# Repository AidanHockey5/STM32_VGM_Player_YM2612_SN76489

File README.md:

# This Version of the Project is now Deprecated
This is the old version of the Mega Blaster Project. Please visit this repo for the latest and greatest Mega Blaster 2 source material
https://github.com/AidanHockey5/MegaBlaster2

# Mega Blaster

See this project in action here: https://www.youtube.com/watch?v=WoAp2-gWaLM

For more information, visit: http://www.aidanlawrence.com/megablaster-hardware-sega-genesis-video-game-music-player/

This project is a hardware Video Game Music (VGM) player that uses a genuine YM2612 synthesizer chip + SN76489AN PSG. 
This project is driven by an STM32 "Blue Pill" board, chosen for it's ample speed, I/O, and best of all, price!

Included in this repository is the source code for the project, all of the schematic files, and a completed 
Ki-CAD printed circuit board /w Gerber files. Feel free to produce your own board!

# Information about the main sound chips and VGM

The YM2612 is a 6-channel FM synthesizer IC that was most prominently featured in the Sega Genesis (AKA Megadrive) home video game console. The YM2612 was also featured in the FM-Towns home computer and the Sega C2 Arcade System.
The YM2612 also had a CMOS alias that is functionally identical named the YM3438.
The SN76489 is a 3-channel + 1 noise channel programmable sound generator (PSG) that was popular with several early video game systems and home computers.
Most notably, the SN76489 was featured in the Sega Master system, the predecessor to the Genesis. To allow for backwards compatibility, Sega included a clone of the SN76489 in their new Genesis consoles.
Programmers and sound designers could leverage the SN76489 to add three more square wave channels to the YM2612's 6-channels of FM synth, creating 9 channels + 1 noise channels in total.
While this player was designed with the Genesis in mind, it can play back any VGM files designed for the Master System, FM-Towns PC, C2 machine, or any other machine that used the YM2612/YM3438 and/or the SN76489.
This project synthesizes music from .VGM files in real time on genuine hardware. There is no emulation here.

VGM stands for Video Game Music, and it is a 44.1KHz logging format that stores real soundchip register information. My player will parse these files and send the data to the appropriate chips. You can learn more about the VGM file format here: http://www.smspower.org/Music/VGMFileFormat

http://www.smspower.org/uploads/Music/vgmspec170.txt?sid=58da937e68300c059412b536d4db2ca0

# SD Card Information
This project is built for full-sized SD cards, but you may use adapters to fit your desired card. You must format your SD card to Fat32 in order for this device to work correctly. Your SD card must only contain uncompressed .vgm files. VGZ FILES WILL NOT WORK! You may download .vgz files and use [7zip](http://www.7-zip.org/download.html) to extract the uncompressed file out of them. Vgm files on the SD card do not need to have the .vgm extension. As long as they contain valid, uncompressed vgm data, they will be read by the program regardless of their name.
You can find VGM files by Googling "myGameName VGM," or by checking out sites like http://vgmrips.net/packs/

# Control Over Serial
You can use a serial connection to control playback features. The commands are as follows:

Command | Result
------------ | -------------
\+ | Next Track
\- | Previous Track
\* | Random Track
\/ | Toggle Shuffle Mode
\. | Toggle Song Looping
r: | Request song
? | What song is playing?
\! | Toggle the OLED display

A song request is formatted as follows: ```r:mySongFile.vgm```
Once a song request is sent through the serial console, an attempt will be made to open that song file. The file must exist on the SD card, and spelling/capitalization must be correct.
Need an easy-to-use serial console? [I've made one here.](https://github.com/AidanHockey5/OpenArduinoSerialConsole)

# Schematic

[PDF](https://github.com/AidanHockey5/STM32_VGM_Player_YM2612_SN76489/raw/master/Schematics/STM32_MegaBlaster/STM32_MegaBlaster.pdf)

[Bill Of Materials (BOM)](https://github.com/AidanHockey5/STM32_VGM_Player_YM2612_SN76489/tree/master/Schematics/STM32_MegaBlaster/BOM)

# Interactive Assembly Guide
[You can view the interactive guide here.](https://www.aidanlawrence.com/wp-content/uploads/2018/09/ibom.html)

Courtesy of the stellar KiCAD plugin, [Interactive HTML BOM](https://github.com/openscopeproject/InteractiveHtmlBom)

Use this guide to help you assemble the Mega Blaster. Hover your cursor over the list of parts and this web page will show you where to place each component. I have included the source HTML file under the [Schematic's BOM folder](https://github.com/AidanHockey5/STM32_VGM_Player_YM2612_SN76489/tree/master/Schematics/STM32_MegaBlaster/BOM) for local viewing. 

# Programming

Programming must be done through the built-in serial port. YOU CAN NOT USE AN STLINK FOR PROGRAMMING.

You have two programming options: Using the flashing tool OR flashing from source.

[DOWNLOAD THE FLASHING TOOL HERE](https://www.aidanlawrence.com/tools/ee/megablaster/MegaFlasher_MB.zip)

Windows users can just use the pre-compiled Flash.exe program to skip worrying about Python installs or dependancies.
All other operating system users can simply run the Flash.py script using Python 3.0+.

Read the Readme file included with the tool for usage instructions and python dependancies.

I have also made a quick video guide on how to program the MegaBlaster from source. It's pretty simple!

https://youtu.be/sSx3_d5n6gs

1) Set the "Bluepill" left jumper to the '1' position.
2) Turn on the MegaBlaster
3) Hit the reset button on the Bluepill board.
4) Open the source code in Visual Studio Code /w the PlatformIO extension.
5) Upload the code using the upload button on the bottom ribbon.
6) Replace the jumper on the Bluepill board to it's original '0' position.

Link to VS Code: https://code.visualstudio.com/

PlatformIO install guide: http://docs.platformio.org/en/latest/ide/vscode.html#installation 

PlatformIO Not finding your serial port? Try opening up your Platformio.ini file and adding the following lines:
```
upload_port = COMX

upload_protocol = serial
```

(Make sure to change 'X' to the number of your COM port that the MegaBlaster is connected to. (I.E. COM4, COM8, COM10, etc.)

# KiCad
The schematic and PCB of this project was made in a nightly version of KiCad 5, specifically, 5.0.0 RC2 (dev-493-gd776eaca8)
Since then, the project has been migrated to KiCAD 5 stable.
Please download the latest stable release of KiCAD 5 here: http://kicad-pcb.org/download/

# YM3438 Support
After a little tinkering, I've managed to get a YM3438 working as a replacement for the YM2612. For those that don't know, the YM3438 is functionally equivalent to the YM2612, but is made using a CMOS process. The YM3438 is pin-compatible but it is not a drop-in replacement since the output impedance is significantly higher. Fortunately, all you need to do to get a YM3438 to work is mod a couple resistors.

Resistor Number | Replace with
------------ | -------------
R7 | LEAVE UNPOPULATED
R8 | LEAVE UNPOPULATED
R6 | 1.2K
R9 | 100K
R10 | 100K
R27 | 33K
R30 | 33K
R28 | 150K
R29 | 150K

WARNING! The final sound output volume will be SIGNIFICANTLY HIGHER with this setup. Be sure to start your YM3438 MegaBlaster at the lowest possible volume before turning on the device and slowly increase the volume to prevent equipment damage and or hearing damage.

Why replace the YM2612 with a YM3438? Well, for one, the YM3438 runs very cool while the YM2612s typically get screaming hot during normal operation. The sound quality is also slightly altered with FM synths typically sounding a little more 'sterile' compared to the YM2612's characteristic grit. PCM sample quality is also significantly improved. Later revisions of the Sega Genesis used an ASIC YM3438 instead of a discrete YM2612, so some users may be more familiar with the likes of the YM3438 than the YM2612. It's all personal preference really.

You can see a YM2612/YM3438 comparison video here: https://www.youtube.com/watch?v=jMHRtriv1wM

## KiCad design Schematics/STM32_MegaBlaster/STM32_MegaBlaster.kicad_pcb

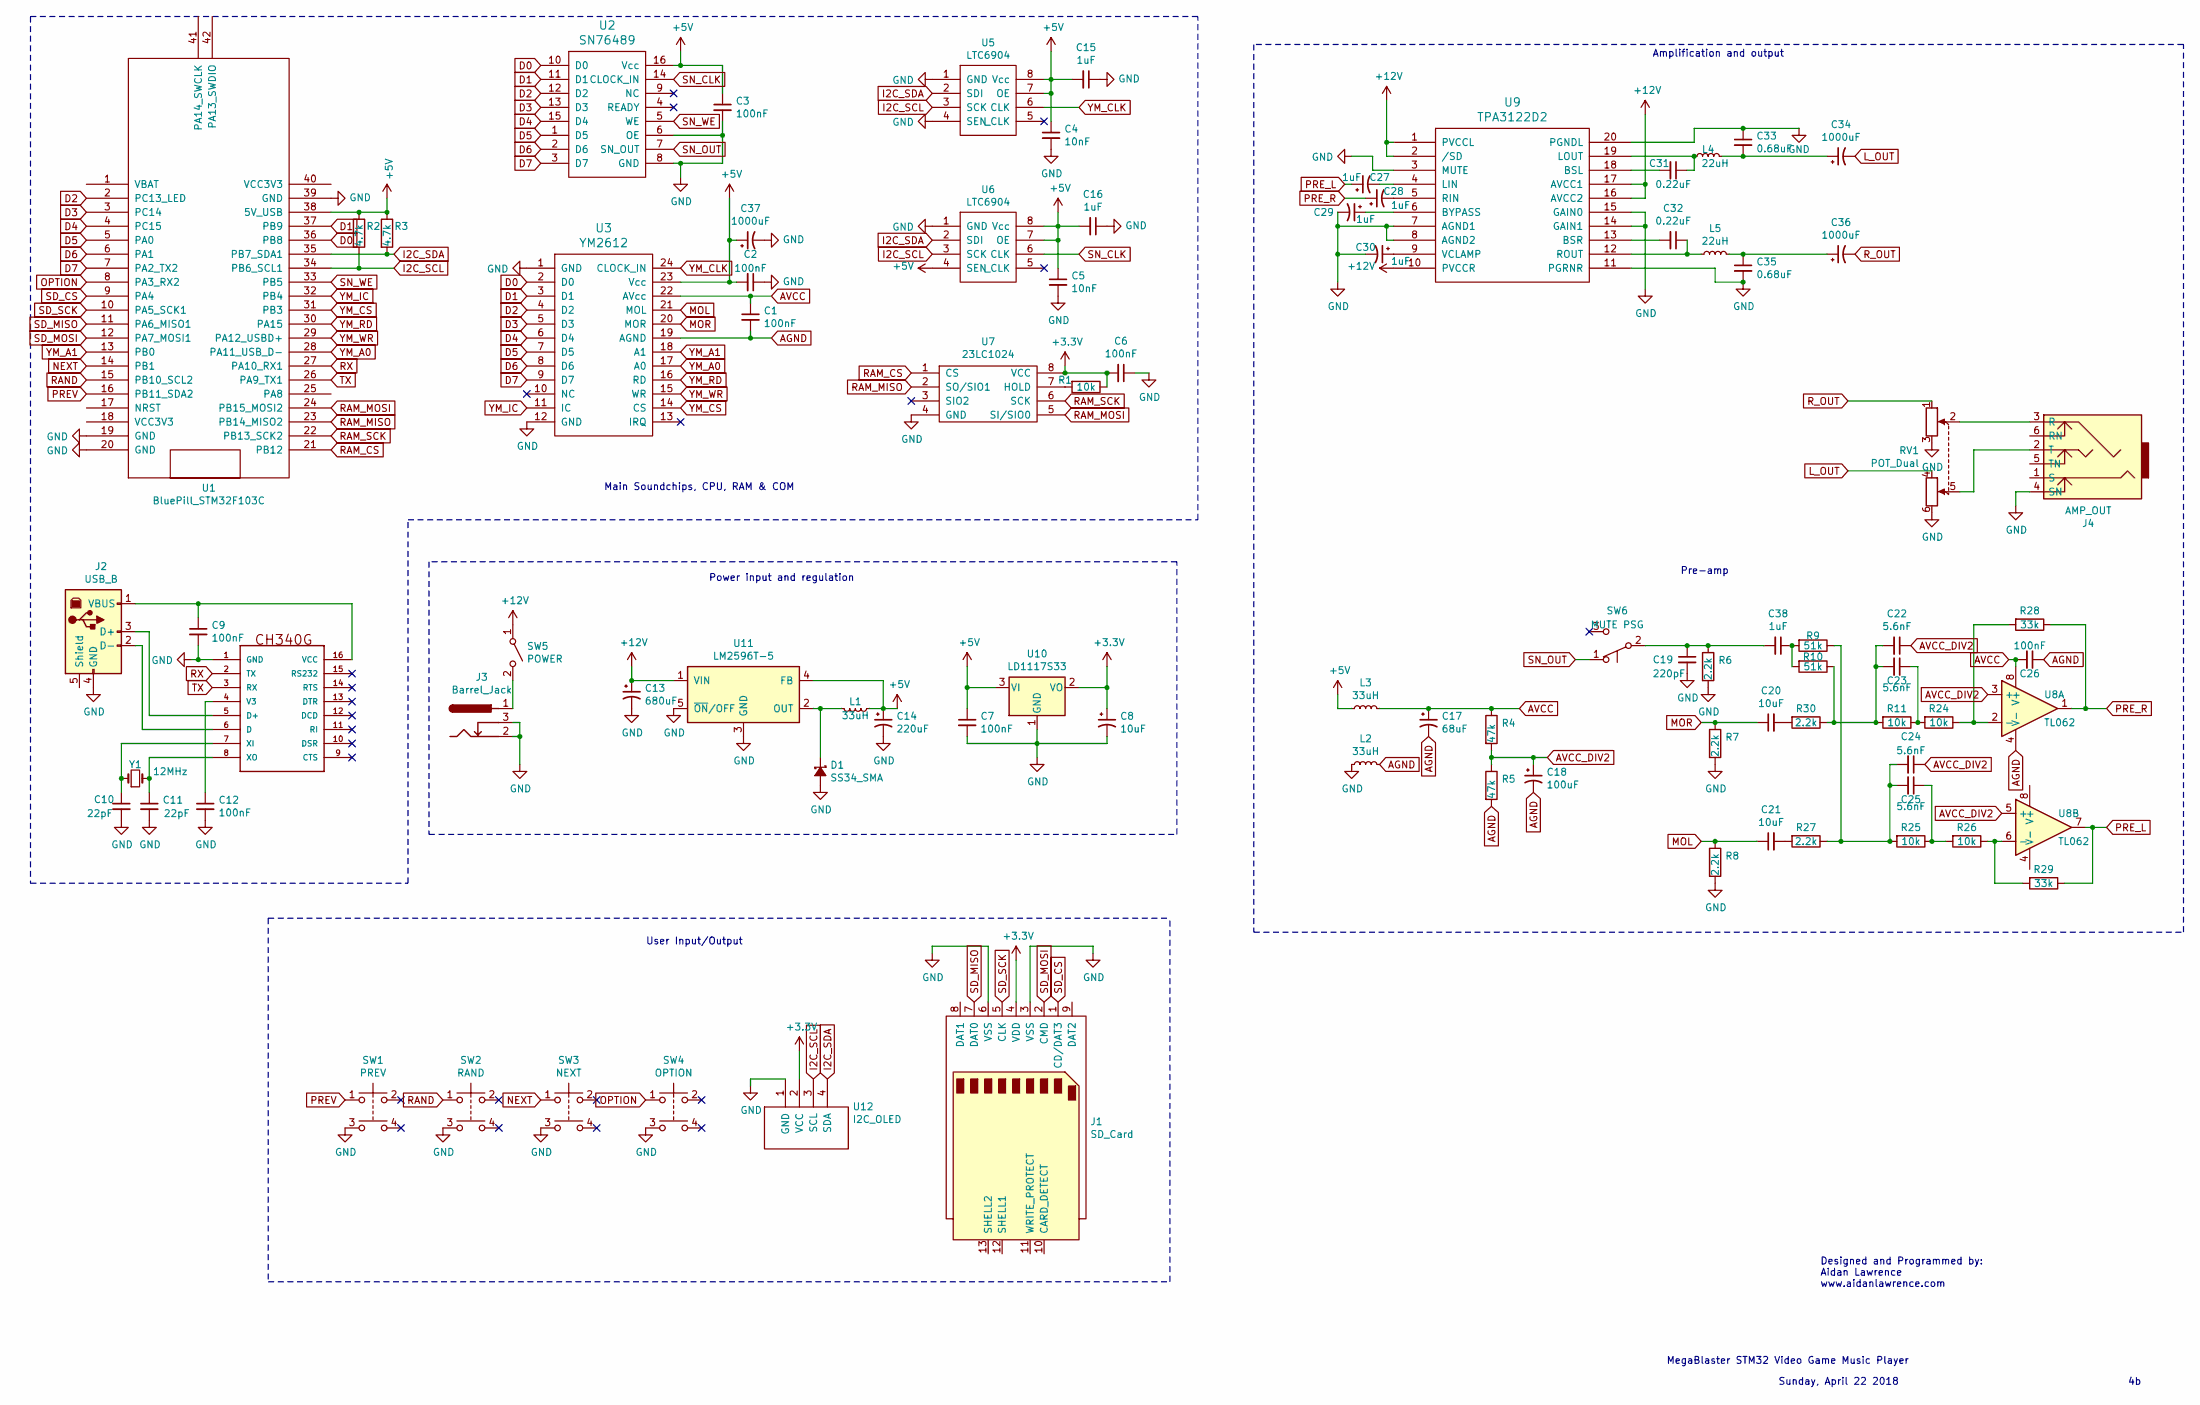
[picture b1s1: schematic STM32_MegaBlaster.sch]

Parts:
C1, C2, C6, C7, C9, C12, C26: 100nF; C_Disc_D3.0mm_W1.6mm_P2.50mm
C3: 100nF; C_Axial_L22.0mm_D10.5mm_P27.50mm_Horizontal
C4, C5: 10nF; C_Disc_D3.0mm_W1.6mm_P2.50mm
C8: 10uF; CP_Radial_D4.0mm_P1.50mm
C10, C11: 22pF; C_Disc_D3.0mm_W1.6mm_P2.50mm
C13: 680uF; CP_Radial_D10.0mm_P5.00mm
C14: 220uF; CP_Radial_D6.3mm_P2.50mm
C15, C16, C38: 1uF; C_Disc_D4.7mm_W2.5mm_P5.00mm
C17: 68uF; CP_Radial_D6.3mm_P2.50mm
C18: 100uF; CP_Radial_D5.0mm_P2.00mm
C19: 220pF; C_Disc_D4.7mm_W2.5mm_P5.00mm
C20, C21: 10uF; C_Disc_D4.7mm_W2.5mm_P5.00mm
C22, C23, C24, C25: 5.6nF; C_Disc_D4.7mm_W2.5mm_P5.00mm
C27, C28, C29, C30: 1uF; CP_Radial_D4.0mm_P1.50mm
C31, C32: 0.22uF; C_Disc_D4.7mm_W2.5mm_P5.00mm
C33: 0.68uF; C_Disc_D3.0mm_W1.6mm_P2.50mm
C34, C36, C37: 1000uF; CP_Radial_D8.0mm_P2.50mm
C35: 0.68uF; CP_Radial_D6.3mm_P2.50mm
D1: SS34_SMA; D_SOD-123F
J1: SD_Card; SD_TE_2041021
J2: USB_B
J3: Barrel_Jack; BARREL_JACK
J4: AMP_OUT; PJ320E_3.5mm_Jack
L1, L2, L3: 33uH; L_Radial_D7.0mm_P3.00mm
L4, L5: 22uH; L_Radial_D8.7mm_P5.00mm_Fastron_07HCP
R1, R11, R24, R25, R26: 10k; R_Axial_DIN0207_L6.3mm_D2.5mm_P7.62mm_Horizontal
R2, R3: 4.7k; R_Axial_DIN0207_L6.3mm_D2.5mm_P7.62mm_Horizontal
R4, R5: 47k; R_Axial_DIN0207_L6.3mm_D2.5mm_P7.62mm_Horizontal
R6, R7, R8, R27, R30: 2.2k; R_Axial_DIN0207_L6.3mm_D2.5mm_P7.62mm_Horizontal
R9, R10: 51k; R_Axial_DIN0207_L6.3mm_D2.5mm_P7.62mm_Horizontal
R28, R29: 33k; R_Axial_DIN0207_L6.3mm_D2.5mm_P7.62mm_Horizontal
RV1: POT_Dual; Potentiometer_Alps_RK163_Double_Vertical
SW1: PREV; SW_TH_Tactile_Omron_B3F-10xx
SW2: RAND; SW_TH_Tactile_Omron_B3F-10xx
SW3: NEXT; SW_TH_Tactile_Omron_B3F-10xx
SW4: OPTION; SW_TH_Tactile_Omron_B3F-10xx
SW5: POWER; 1825115-1
SW6: MUTE PSG; 1825115-1
U1: BluePill_STM32F103C
U2: SN76489; DIP-16_W7.62mm
U3: YM2612; DIP-24_W15.24mm
U4: CH340G; SOIC16
U5, U6: LTC6904; MSOP-8_3x3mm_Pitch0.65mm
U7: 23LC1024; DIP-8_W7.62mm
U8: TL062; DIP-8_W7.62mm
U9: TPA3122D2; DIP-20_W7.62mm
U10: LD1117S33; SOT-223-3_TabPin2
U11: LM2596T-5; TO170P1435X465-6N
U12: I2C_OLED; 1_3_Inch_I2C_OLED
Y1: 12MHz; Crystal_HC49-U_Vertical

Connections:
+3V3: C6.2, C8.1, J1.4 (VDD), R1.1, U7.8 (VCC), U10.2 (VO), U12.2 (VCC)
+5V: C2.2, C3.1, C4.1, C5.1, C7.1, C14.1, C15.2, C16.2, C37.1, L1.1, L3.1, R2.1, R3.1, U1.38 (5V_USB), U2.16 (Vcc), U3.23 (Vcc), U5.7 (OE), U5.8 (Vcc), U6.4 (SEN), U6.7 (OE), U6.8 (Vcc), U10.3 (VI), U11.4 (FB)
+12V: C13.1, SW5.1 (A), U9.1 (PVCCL), U9.2 (/SD), U9.10 (PVCCR), U9.16 (AVCC2), U9.17 (AVCC1), U11.1 (VIN)
AGND: C1.2, C17.2, C18.2, C26.1, L2.2, R5.2, U3.19 (AGND), U8.4 (V-)
AVCC: C1.1, C17.1, C26.2, L3.2, R4.1, U3.22 (AVcc), U8.8 (V+)
AVCC_DIV2: C18.1, C22.1, C24.1, R4.2, R5.1, U8.3 (+), U8.5 (+)
D0: U1.36 (PB8), U2.10 (D0), U3.2 (D0)
D1: U1.37 (PB9), U2.11 (D1), U3.3 (D1)
D2: U1.2 (PC13_LED), U2.12 (D2), U3.4 (D2)
D3: U1.3 (PC14), U2.13 (D3), U3.5 (D3)
D4: U1.4 (PC15), U2.15 (D4), U3.6 (D4)
D5: U1.5 (PA0), U2.1 (D5), U3.7 (D5)
D6: U1.6 (PA1), U2.2 (D6), U3.8 (D6)
D7: U1.7 (PA2_TX2), U2.3 (D7), U3.9 (D7)
GND: C2.1, C3.2, C4.2, C5.2, C6.1, C7.2, C8.2, C9.2, C10.2, C11.2, C12.2, C13.2, C14.2, C15.1, C16.1, C19.2, C29.2, C30.2, C33.1, C35.2, C37.2, D1.2 (A), J1.3 (VSS), J1.6 (VSS), J2.4 (GND), J3.2, J3.3, J4.3 (R), J4.4 (SN), L2.1, R6.2, R7.2, R8.2, RV1.2, RV1.3, RV1.6, SW1.3, SW2.3, SW3.3, SW4.3, U1.19 (GND), U1.20 (GND), U1.39 (GND), U2.6 (OE), U2.8 (GND), U3.1 (GND), U3.12 (GND), U4.1 (GND), U5.1 (GND), U5.4 (SEN), U6.1 (GND), U7.4 (GND), U9.3 (MUTE), U9.7 (AGND1), U9.8 (AGND2), U9.11 (PGRNR), U9.14 (GAIN1), U9.15 (GAIN0), U9.20 (PGNDL), U10.1 (GND), U11.3 (GND), U11.5 (~ON~/OFF), U11.6, U12.1 (GND); also elsewhere on the board
I2C_SCL: R2.2, U1.34 (PB6_SCL1), U5.3 (SCK), U6.3 (SCK), U12.3 (SCL)
I2C_SDA: R3.2, U1.35 (PB7_SDA1), U5.2 (SDI), U6.2 (SDI), U12.4 (SDA)
L_OUT: C34.2, RV1.4; also elsewhere on the board
MOL: C21.1, R8.1, U3.21 (MOL)
MOR: C20.1, R7.1, U3.20 (MOR)
NEXT: SW3.1, U1.14 (PB1); also elsewhere on the board
unnamed: C9.1, J2.1 (VBUS), U4.16 (VCC)
unnamed: C10.1, U4.7 (XI), Y1.1
unnamed: C11.1, U4.8 (XO), Y1.2
unnamed: C12.1, U4.4 (V3)
unnamed: C19.1, C38.2, R6.1, SW6.2 (B)
unnamed: C20.2, R30.2
unnamed: C21.2, R27.2
unnamed: C22.2, C23.2, R10.1, R11.2, R30.1
unnamed: C23.1, R11.1, R24.2
unnamed: C24.2, C25.2, R9.1, R25.2, R27.1
unnamed: C25.1, R25.1, R26.2
unnamed: C27.2, U9.4 (LIN)
unnamed: C28.2, U9.5 (RIN)
unnamed: C29.1, U9.6 (BYPASS)
unnamed: C30.1, U9.9 (VCLAMP)
unnamed: C31.1, L4.1, U9.19 (LOUT)
unnamed: C31.2, U9.18 (BSL)
unnamed: C32.1, L5.1, U9.12 (ROUT)
unnamed: C32.2, U9.13 (BSR)
unnamed: C33.2, C34.1, L4.2
unnamed: C35.1, C36.1, L5.2
unnamed: C38.1, R9.2, R10.2
unnamed: D1.1 (K), L1.2, U11.2 (OUT)
unnamed: J2.2 (D-), U4.6 (D)
unnamed: J2.3 (D+), U4.5 (D+)
unnamed: J3.1, SW5.2 (B)
unnamed 53: J4.1 (S); also elsewhere on the board
unnamed 54: J4.2 (T), RV1.5; also elsewhere on the board
unnamed: R1.2, U7.7 (HOLD)
unnamed: R24.1, R28.2, U8.2 (-)
unnamed: R26.1, R29.2, U8.6 (-)
OPTION: SW4.1, U1.8 (PA3_RX2); also elsewhere on the board
PREV: SW1.1, U1.16 (PB11_SDA2); also elsewhere on the board
PRE_L: C27.1, R29.1, U8.7
PRE_R: C28.1, R28.1, U8.1
RAM_CS: U1.21 (PB12), U7.1 (CS)
RAM_MISO: U1.23 (PB14_MISO2), U7.2 (SO/SIO1)
RAM_MOSI: U1.24 (PB15_MOSI2), U7.5 (SI/SIO0)
RAM_SCK: U1.22 (PB13_SCK2), U7.6 (SCK)
RAND: SW2.1, U1.15 (PB10_SCL2); also elsewhere on the board
RX: U1.27 (PA10_RX1), U4.2 (TX)
R_OUT: C36.2, RV1.1; also elsewhere on the board
SD_CS: J1.1 (CD/DAT3), U1.9 (PA4)
SD_MISO: J1.7 (DAT0), U1.11 (PA6_MISO1)
SD_MOSI: J1.2 (CMD), U1.12 (PA7_MOSI1)
SD_SCK: J1.5 (CLK), U1.10 (PA5_SCK1)
SN_CLK: U2.14 (CLOCK_IN), U6.6 (CLK)
SN_OUT: SW6.1 (A), U2.7 (SN_OUT)
SN_WE: U1.33 (PB5), U2.5 (WE)
TX: U1.26 (PA9_TX1), U4.3 (RX)
YM_A0: U1.28 (PA11_USB_D-), U3.17 (A0)
YM_A1: U1.13 (PB0), U3.18 (A1)
YM_CLK: U3.24 (CLOCK_IN), U5.6 (CLK)
YM_CS: U1.31 (PB3), U3.14 (CS)
YM_IC: U1.32 (PB4), U3.11 (IC)
YM_RD: U1.30 (PA15), U3.16 (RD)
YM_WR: U1.29 (PA12_USBD+), U3.15 (WR)

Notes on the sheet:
MegaBlaster STM32 Video Game Music Player
Sunday, April 22 2018
Designed and Programmed by: Aidan Lawrence www.aidanlawrence.com
Main Soundchips, CPU, RAM & COM
Power input and regulation
User Input/Output
Amplification and output
Pre-amp

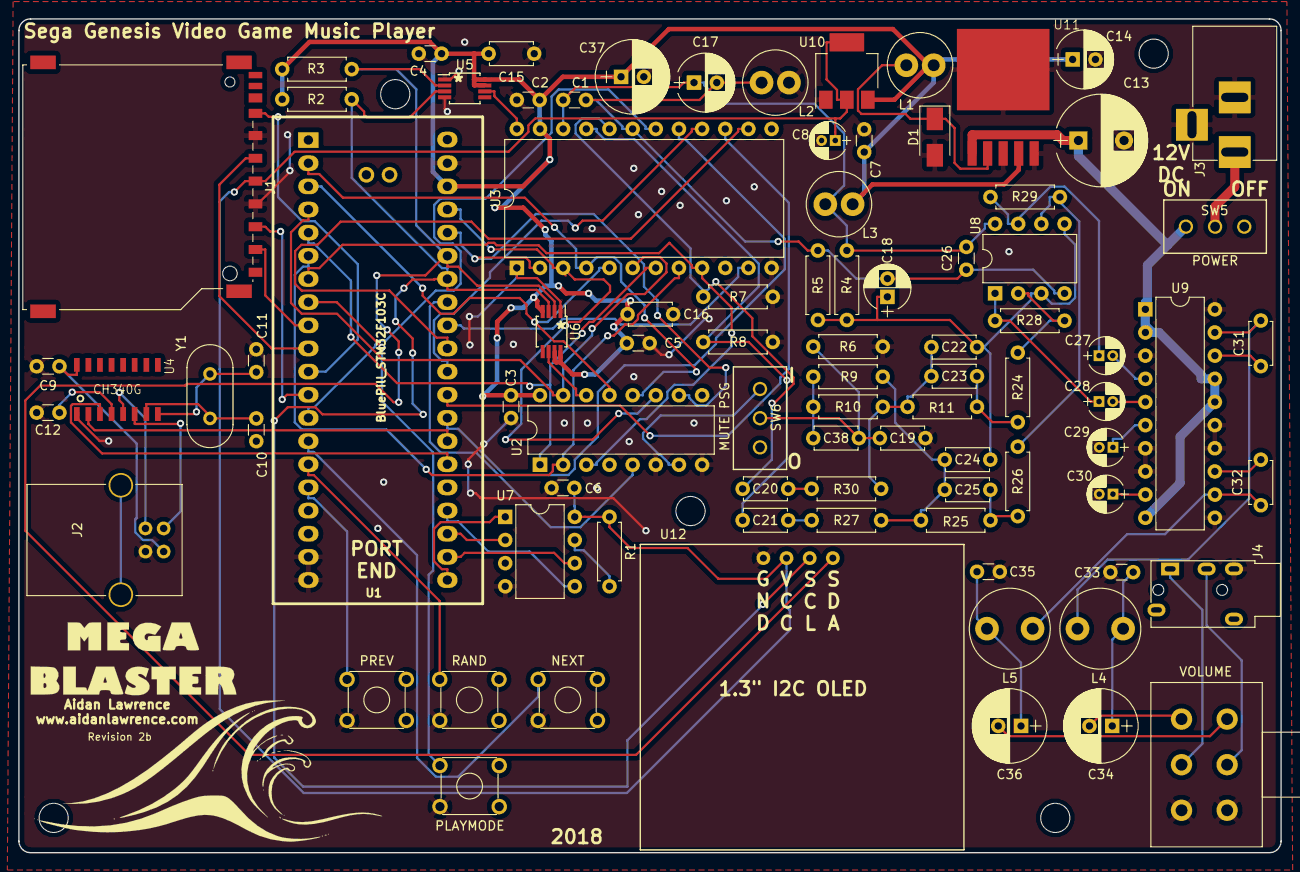
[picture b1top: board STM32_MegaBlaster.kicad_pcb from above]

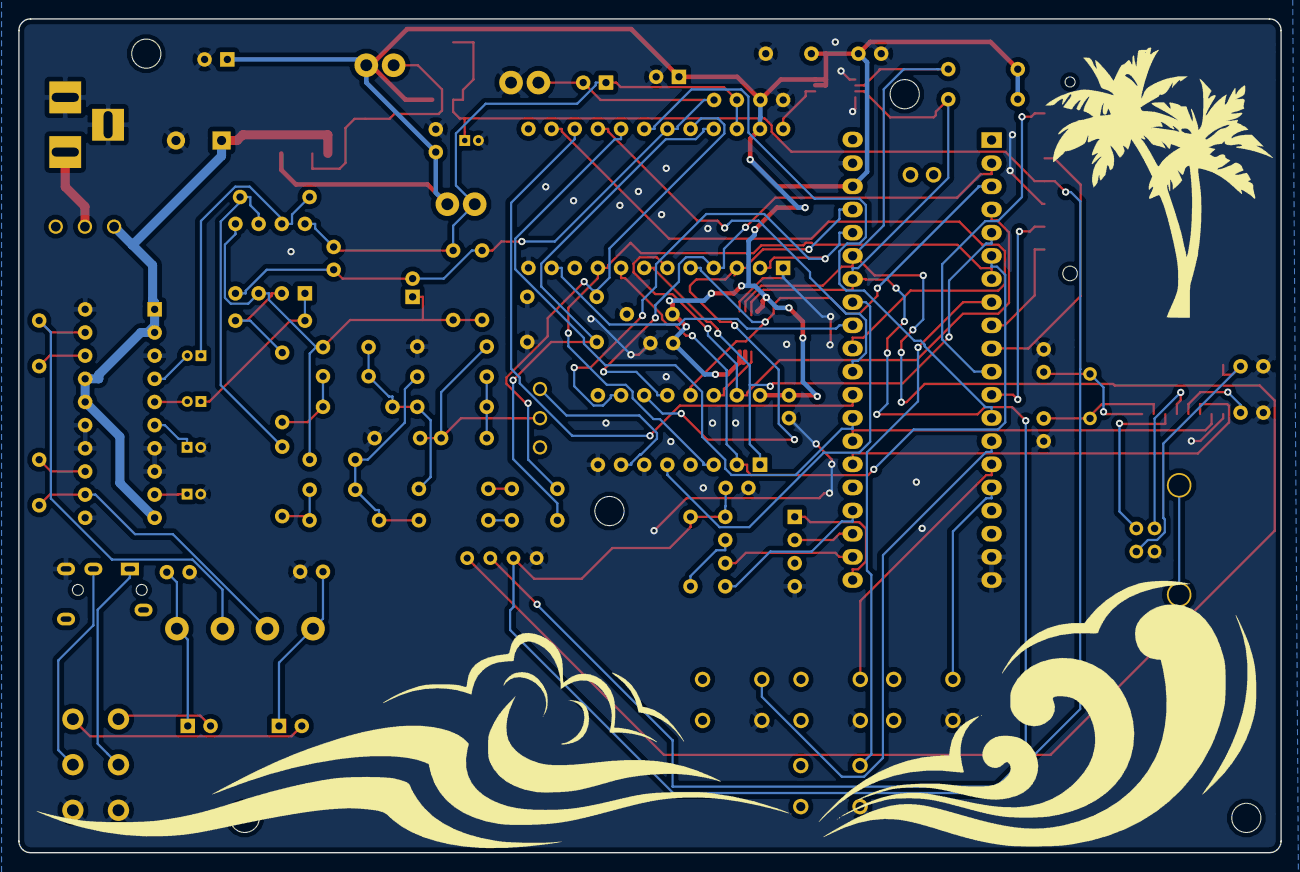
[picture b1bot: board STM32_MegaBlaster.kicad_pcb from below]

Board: 2 copper layers, 138.4 x 91.4 mm, 95 parts (2 on the bottom side), 78 nets.

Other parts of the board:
G1: LOGO; wave1
G2: LOGO; mega_blaster_logo
G3: LOGO; wave2
G4: LOGO; trees
H1, H1#2, H1#3, H1#4, H1#5: MountingHole_3.2mm_M3
NEXT: NEXT; SW_TH_Tactile_Omron_B3F-10xx
PLAYMODE: OPTION; SW_TH_Tactile_Omron_B3F-10xx
PREV: PREV; SW_TH_Tactile_Omron_B3F-10xx
RAND: RAND; SW_TH_Tactile_Omron_B3F-10xx
VOLUME: POT_Dual; Potentiometer_Alps_RK163_Double_Vertical(SWAP)

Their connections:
GND: NEXT.3, PLAYMODE.3, PREV.3, RAND.3, VOLUME.3, VOLUME.6; also elsewhere on the board
L_OUT: VOLUME.4; also elsewhere on the board
NEXT: NEXT.1; also elsewhere on the board
unnamed 53: VOLUME.5; also elsewhere on the board
unnamed 54: VOLUME.2; also elsewhere on the board
OPTION: PLAYMODE.1; also elsewhere on the board
PREV: PREV.1; also elsewhere on the board
RAND: RAND.1; also elsewhere on the board
R_OUT: VOLUME.1; also elsewhere on the board

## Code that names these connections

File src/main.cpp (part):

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uint16_t parseVGM();


Bus bus(PB8, PB9, PC13, PC14, PC15, PA0, PA1, PA2);

YM2612 opn(&bus, PB3, NULL, PA12, PA11, PB0, PB4);
SN76489 sn(&bus, PB5);

//OLED
U8G2_SH1106_128X64_NONAME_F_HW_I2C oled(U8G2_R0);
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//Buttons
const int prev_btn = PB11;
const int rand_btn = PB10;
const int next_btn = PB1;
const int option_btn = PA3;

//SD & File Streaming
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  oled.clearDisplay();

  //SD
  if(!SD.begin(PA4, SD_SCK_HZ(F_CPU/2)))
  {
    Serial.println("SD Mount Failed!");
    oled.clearBuffer();
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
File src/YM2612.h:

#ifndef YM2612_H_
#define YM2612_H_
#include <Arduino.h>
#include "Bus.h"
class YM2612
{
private:
    Bus * _bus;
public:
    YM2612(Bus * bus);
    void Reset();
    void Send(unsigned char addr, unsigned char data, bool setA1);
};
#endif

//Notes
//YM_CS = PB3
//YM_RD = PA15
//YM_WR = PA12
//YM_A0 = PA11
//YM_A1 = PB0
//YM_IC = PB4 

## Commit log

2018-03-07 Starting to port code to STM32 platform
2018-03-07 FM Portion of player works. PCM samples are causing issues with external SPI RAM.
2018-03-25 Update LICENSE
2018-04-02 Fixed PCM/RAM bug. STM32 plays vgm music, but seems to be a tad too slow for consistent playback.
2018-04-16 New FAST GPIO direct access. Full PCM support via external RAM. Sounding great!
2018-04-22 Added OLED support. Beginning schematic
2018-04-23 Saving schematic. Nearly Complete
2018-04-23 Schematic complete. Now working on PCB
2018-04-27 PCB near complete
2018-04-28 PCB Complete
2018-05-02 Moved gnd trace
2018-05-05 Correct amplifier circuit and changed a couple footprints
2018-05-05 Corrected headphone jack
2018-05-06 Added OLED toggle
2018-05-07 Changed diode to more friendly package, moved OLED I2C lines far away from mixer circuit
2018-05-12 Fixed PCM and loop offset
2018-05-14 Readme and schematic plots
2018-05-17 Added NTSC/PAL rate adjustments for sound chip clocks
2018-05-18 Added better BOM
2018-05-18 Force upload library files
2018-05-19 Updated schematics and gerber files
2018-05-20 Comment correction and changed SPI mode for SD card
2018-06-04 Changed playmode indicators and turned off unused LTC6904 inverted outputs.
2018-06-04 Added SN76489 reset in setup to prevent rogue noises on startup
2018-06-10 Added programming guide
2018-06-10 Changed BOM to include 1000uF capacitors that fit a little better
2018-06-10 Corrected L4, L5 Inductor. 22uH to 2.2mH
2018-06-22 Added mini-guide for YM3438 support
2018-06-22 Added YM3438 Mini-guide
2018-06-23 Added video link to YM2612/YM3438 comparison video
2018-07-09 Fixed random song crash if only one track is present on SD card.
2018-07-29 + local RAM PCM Buffer to help speed up songs with small PCM sample sizes.
2018-07-30 Added toggle for local PCM buffer option
2018-08-25 Replaced private BOM link with public cart link
2018-09-07 Removed polarized cap symbol for C20, C21
2018-09-07 Added interactive HTML BOM guide
2018-09-07 Added info on new interactive BOM
2018-10-28 Beginning refactor with new bus
2018-10-28 Cleaned up soundchip drivers and added new bus system
2018-10-29 New player has basic PSG support and sounds much better!
2018-10-29 Saving. Need to fix loop still
2018-10-29 Added PCM RAM caching and playback
2018-10-30 VGM header read, loop adjust. Need to rewrite RAM driver for SEQ reading
2018-10-30 notes
2018-10-31 loop glitch fixed. Added loop prebuffer. Added RAM precache
2018-11-01 Added button + serial control. Proper VGM header reading. VGM indent check. Added track navigation
2018-11-01 Added chip resets and clock adjusting after every file load
2018-11-01 Moved command playback to tick interrupt. Various bug fixes
2018-11-02 Added english GD3
2018-11-02 Fixed crash due to serial call in interrupt. Need to fix odd error'd out command bytes
2018-11-02 Fixed crash on VGM files that were smaller than the main buffer
2018-11-03 Save
2018-11-04 New ring buffer. Loop crash fixed. Non-looping VGMs have issues on loop
2018-11-04 Added buffer check on tick
2018-11-05 New logo, OLED support in. bug fixes.
2018-11-05 Feature parity complete, Version 2 ready for release
2018-11-11 Update platformio.ini
    Added upload notes
2018-11-18 Remove useless serial wait
2019-01-26 Fixed inductor values on ibom.html
2019-02-05 Fixed SN76489 typo on schematic
2019-02-07 Added PIO command for legacy STM32 libs
2019-02-07 Natalie has a keen eye for typos
2019-03-03 Changed local u8g2 to pio edition, removed extra STM32 'platform'
2019-03-08 Set platform = ststm32@~3.8.0
2019-04-06 Changed pinouts to add 8/4MHz clockout
2019-04-10 PSG Noise channel fixed. Hi-hats are back!
2019-05-27 New VGM driver backported
2019-05-27 commented upload port option
2019-05-29 Fixed accidentally commented portion of bus driver
2019-06-30 Disable debug ports
2019-07-26 Schematic correction
2019-08-11 Create LICENSE
2019-08-11 Rename LICENSE to LICENSE.md
2020-03-28 New meta file remover function to prevent crashs from system files.
2020-03-28 New meta file remover function to prevent crashes from system files.
2020-03-28 commented upload port
2020-10-18 Corrected vgm parsing error. Smooth brain moment
2021-01-01 New VGM Engine, yay!
2021-01-01 Fixed VGM parser compensation
2021-01-01 Memory leak fixed
2021-01-01 new logo
2021-01-01 New VGM Engine
2021-01-02 New bug: Device wont play files when in 00 boot in config
2021-01-02 New clock system caused issues with boot pin 00 config. Removing for now.
2021-01-02 Revert version of SDFat
2021-01-03 Removed ready bool from vgm parser to improve playback speed
2021-01-04 Fixed YM write errors
2021-01-05 Added flashing tool

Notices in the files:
parts and their libraries:
Copyright 2016 Accelerated Designs. All rights reserved.
